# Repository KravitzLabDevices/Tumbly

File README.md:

# Tumbly

An Arduino library for the Tumbly device, a time-restricted feeding device. 

**Hardware:** Adafruit Feather M0, OLED FeatherWing (SH1107), RTC FeatherWing, SD card, Servo  

See the [Wiki](https://github.com/KravitzLabDevices/Tumbly/wiki) for build instructions.

Based on the [Tumble Feeder](https://pubmed.ncbi.nlm.nih.gov/40541188/).

## License

GPL-3.0

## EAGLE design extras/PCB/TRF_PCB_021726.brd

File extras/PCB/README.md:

Order the custom PCB (you can download BRD and SCH files from the extras directory and have this made anywhere, or click this link to order the PCB from OshPark)

<a href="https://oshpark.com/shared_projects/LoxoiB0y"></img></a>

  <br>

Assembly instructions:  
1) Populate the custom PCB:  

2) Add stacking headers to the Adafruit DS3231 RTC board and Adafruit M0 Adalogger

3) Stack the four boards together - that's it!

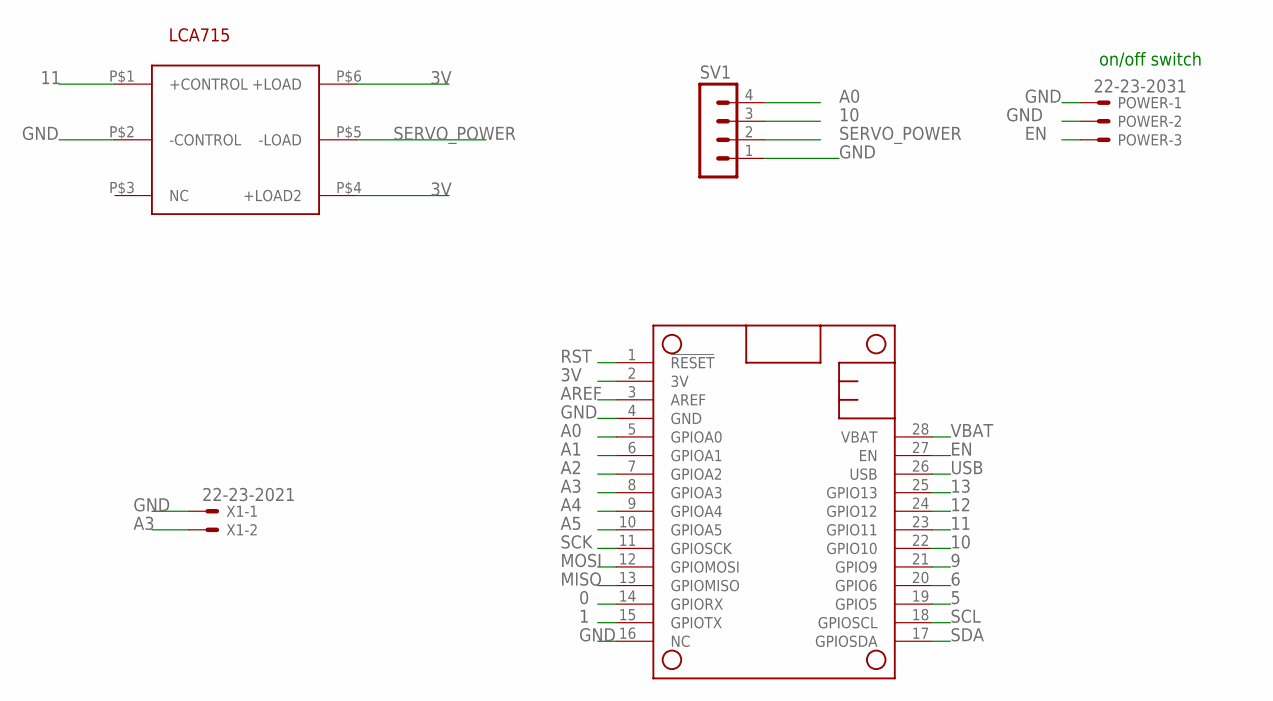
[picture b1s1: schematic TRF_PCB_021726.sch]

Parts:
MS2: MICROSHIELD_NODIM; MICROSHIELD_DIM
POWER: 22-23-2031
SSR3: LCA715S; LCA7XX
SV1: MA04-1
X1: 22-23-2021

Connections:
0: MS2.14 (GPIORX)
1: MS2.15 (GPIOTX)
3V: MS2.2 (3V), SSR3.P$4 (+LOAD2), SSR3.P$6 (+LOAD)
5: MS2.19 (GPIO5)
6: MS2.20 (GPIO6)
9: MS2.21 (GPIO9)
10: MS2.22 (GPIO10), SV1.3
11: MS2.23 (GPIO11), SSR3.P$1 (+CONTROL)
12: MS2.24 (GPIO12)
13: MS2.25 (GPIO13)
A0: MS2.5 (GPIOA0), SV1.4
A1: MS2.6 (GPIOA1)
A2: MS2.7 (GPIOA2)
A3: MS2.8 (GPIOA3), X1.2
A4: MS2.9 (GPIOA4)
A5: MS2.10 (GPIOA5)
AREF: MS2.3 (AREF)
EN: MS2.27 (EN), POWER.3
GND: MS2.4 (GND), MS2.16 (NC), POWER.1, POWER.2, SSR3.P$2 (-CONTROL), SV1.1, X1.1
MISO: MS2.13 (GPIOMISO)
MOSI: MS2.12 (GPIOMOSI)
RST: MS2.1 (!RESET)
SCK: MS2.11 (GPIOSCK)
SCL: MS2.18 (GPIOSCL)
SDA: MS2.17 (GPIOSDA)
SERVO_POWER: SSR3.P$5 (-LOAD), SV1.2
USB: MS2.26 (USB)
VBAT: MS2.28 (VBAT)

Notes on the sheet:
on/off switch

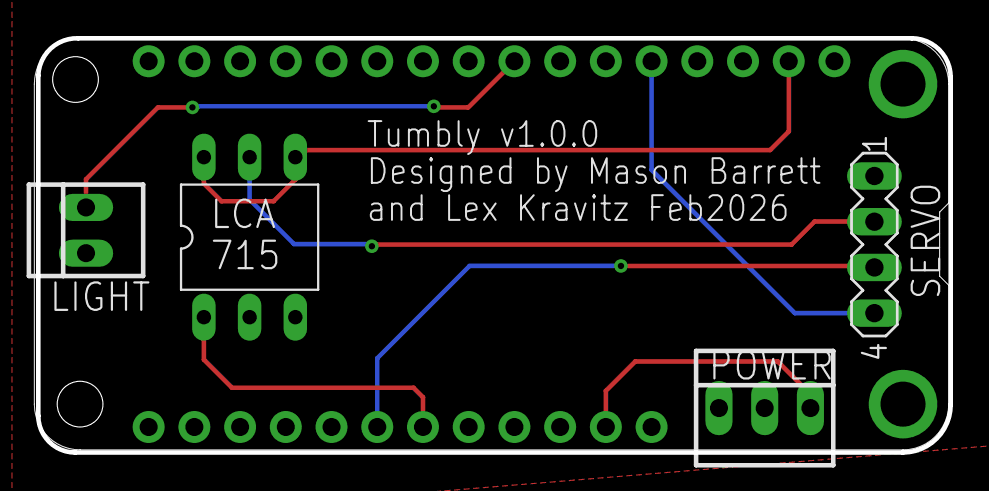
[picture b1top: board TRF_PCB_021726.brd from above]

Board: 2 copper layers, 50.7 x 23.0 mm, 5 parts (0 on the bottom side), 8 nets.

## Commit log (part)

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2026-02-18 Add PCB design and Arduino firmware files
    Add complete Eagle PCB files and board images plus the Arduino firmware source. Files added: extras/PCB (TRF_PCB_021726.brd, .sch, Top.png, Bottom.png) and src/*.ino modules (Battery, Display, Door, 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
2026-02-18 Refactor into Tumbly Arduino library
    Merge legacy INO sketches into a proper Arduino library: add src/Tumbly.cpp and src/Tumbly.h with a public API (begin, run, setDeviceId, setSleepTime, setDoorTimes, setDoorPositions, and helpers). Ad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
2026-02-18 Rename example to Tumbly
    Rename the example directory and sketch from examples/SimpleCastle_OLED_SleepyScreen/SimpleCastle_OLED_SleepyScreen.ino to examples/Tumbly/Tumbly.ino. The file contents are unchanged (100% similarity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
2026-02-18 Refactor README for installation and usage clarity
    Removed manual installation instructions and updated usage example with commented-out configuration options.
2026-02-18 Revise README for clarity and updated links
    Updated hardware description and references in README.
2026-02-18 Improve README formatting and add Wiki link
    Updated hardware list formatting and added link to Wiki for build instructions.
2026-02-18 Update README with hardware details and wiki link
    Added hardware specifications and wiki link for instructions.
2026-02-18 Remove installation and usage sections from README
    Removed installation and usage instructions for Tumbly library.
2026-02-24 Add 3D design STLs and PCB README extras
    Add 3D printing assets and documentation for the Tumbly project: three STL files (Tumbly_Base.stl, Tumbly_Door.stl, Tumbly_Hopper.stl) under extras/3D_Design and README.md files for extras/3D_Design 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
2026-02-24 Update README for clarity on 3D printing files
2026-02-24 Revise PCB README with ordering details and images
    Updated README to include ordering information and images.
2026-02-24 Add TinkerCAD design link to README.md
    Added a link to the editable TinkerCAD design for the 3D model.
2026-02-24 Update README with PCB assembly instructions
    Added instructions for populating the custom PCB and stacking headers.
2026-02-24 Adjust image sizes and formatting in README.md
    Updated image sizes in PCB assembly instructions and added line breaks.
2026-02-24 Enhance README with images for PCB assembly steps
    Added images to the README for better visualization of the PCB stacking process.
2026-04-16 UI and settings improvements
    Fixed door close time off-by-1 hour. Light sensor now logs and displays "Light"/"Dark" instead of raw values. Settings menu no longer auto-starts — requires button press. Added device ID editor to se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
2026-04-16 Config saving, SD enforcement, wake fix, FreeFeeding task
    Device now saves and loads settings from config.txt on the SD card. SD card is required to start. Wake button works reliably every sleep cycle. Added FreeFeeding task with on-device task selection.
2026-05-21 Task Edits
2026-05-24 Task updates
2026-05-24 Bump version from 1.1.0 to 1.2.0
2026-05-26 Couldnt change tasks in demo mode
2026-05-26 Update parts list date to 05/26/2026
2026-06-02 Fixed bugs
2026-06-02 Removed folder
2026-06-03 Bug fixes
